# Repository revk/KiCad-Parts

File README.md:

# KiCad-Parts

Now on [CodeBerg](https://codeberg.org/RevK/KiCad-Parts)

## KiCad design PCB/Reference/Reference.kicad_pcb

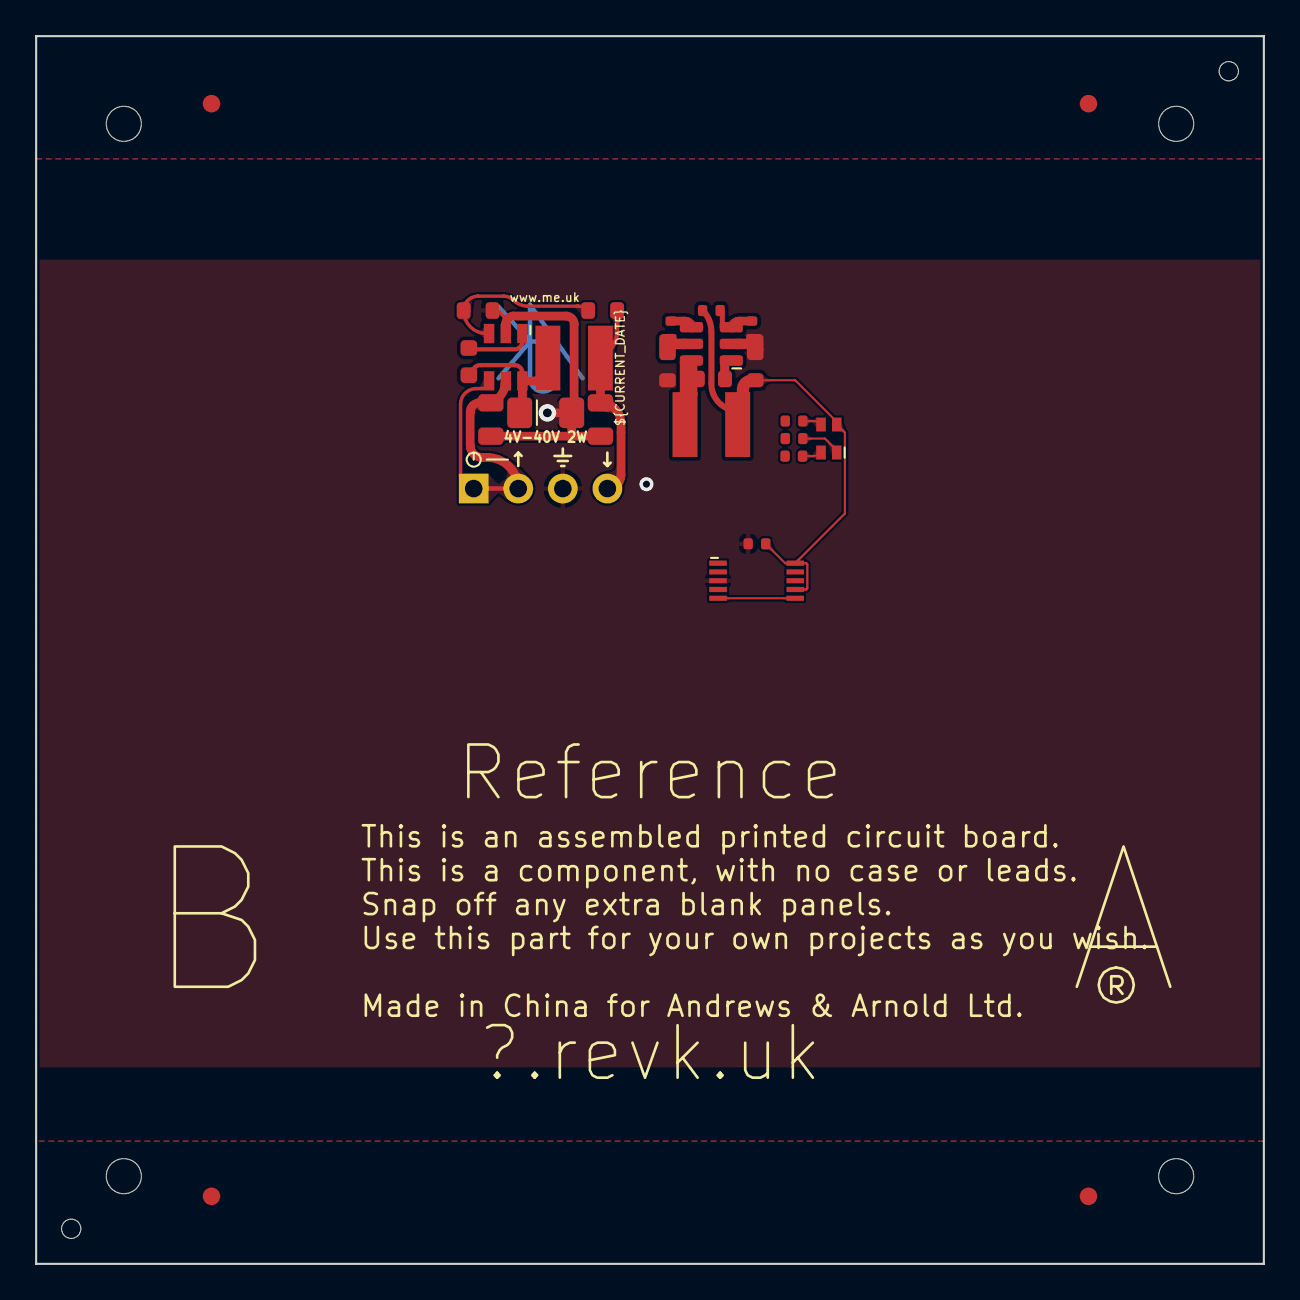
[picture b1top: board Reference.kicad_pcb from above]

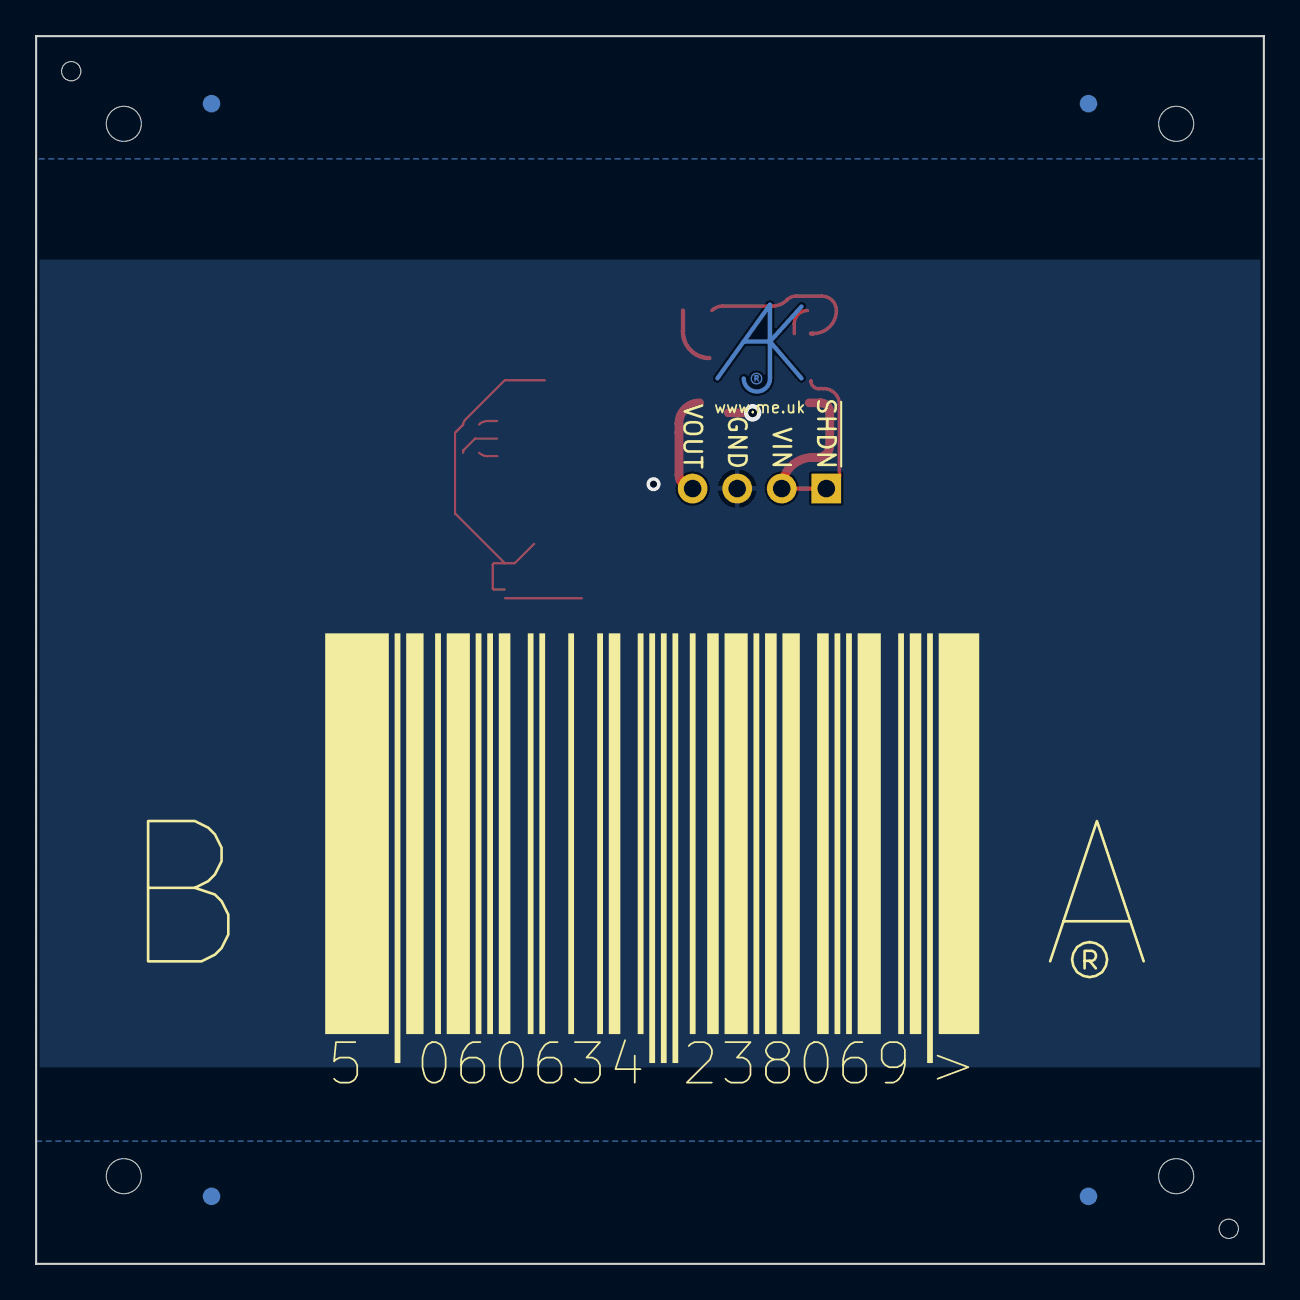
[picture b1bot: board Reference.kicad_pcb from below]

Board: 2 copper layers, 70.0 x 70.0 mm, 28 parts (2 on the bottom side), 9 nets.

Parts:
C1, C6: 100nF; C_0603_
C2: 2.2uF; C_0805_
C3: 10uF; C_0805_
C4: 10uF 50V; C_0603_
C5: 10uF 6.3V; C_0603_
C7: 0.1uF; C_0402
D1: Schottky; D_1206_
D2: RGB; LED-RGB-1.6x1.6
J1: Conn_01x04; JLC-PinHeader_1x04_P2.54mm_Right
L1: 6.8uH; L_4x4_
L2: 10uH; L_4x4_
Logo1: AJK
PCB1: 70x70; PCB7070
R1: 100k 1%; R_0603
R2: 30k 1%; R_0603
R3: 124k; R_0402_
R4: 40k2; R_0402_
R5: 1M; R_0402_
R6: 680R; R_0402
R7: 2K; R_0402
R8: 220R; R_0402
U1: LMR16006XDDCR; SOT-23-Thin-6-Reg
U2: MD8942; SOT-23-6-MD8942
U3: Barcode; EAN-5060634238069
U4: CH340X
V1, V2: VCUT70

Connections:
+3.3V: C7.1, D2.4 (A), U2.8 (VOUT), U4.7 (VCC), U4.10 (V3)
BOOT: U4.5 (~CTS), U4.6 (TNOW/~DTR)
GND: C7.2, J1.3, R2.1, U1.2 (GND), U2.2 (GND), U2.7 (GND), U4.3 (GND)
unnamed: D2.2 (BK), R8.1
unnamed: D2.3 (GK), R7.1
unnamed: D2.1 (RK), R6.1
unnamed: J1.1, J1.2, U1.4 (SHDN), U1.5 (VIN)
unnamed: J1.4, R1.1, U1.7 (VOUT)
unnamed: R1.2, R2.2, U1.3 (FB)

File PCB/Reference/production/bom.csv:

Designator,Footprint,Quantity,Value,LCSC Part #
C1,C_0603_,1,100nF,C30926
C2,C_0805_,1,2.2uF,C19110
C3,C_0805_,1,10uF,C17024
C4,C_0603_,1,10uF 50V,C1591
C5,C_0603_,1,10uF 6.3V,C1691
C6,C_0603_,1,100nF,
C7,C_0402,1,0.1uF,
D1,D_1206_,1,Schottky,C143805
D2,LED-RGB-1.6x1.6,1,RGB,C264508
J1,JLC-PinHeader_1x04_P2.54mm_Right,1,Conn_01x04,C91552
L1,L_4x4_,1,6.8uH,C354575
L2,L_4x4_,1,10uH,
R1,R_0603,1,100k 1%,C14675
R2,R_0603,1,30k 1%,C100001
R3,R_0402_,1,124k,
R4,R_0402_,1,40k2,
R5,R_0402_,1,1M,
R6,R_0402,1,680R,
R7,R_0402,1,2K,
R8,R_0402,1,220R,
U1,SOT-23-Thin-6-Reg,1,LMR16006XDDCR,C87080
U2,SOT-23-6-MD8942,1,MD8942,C2684786
U4,CH340X,1,CH340X,C3035748

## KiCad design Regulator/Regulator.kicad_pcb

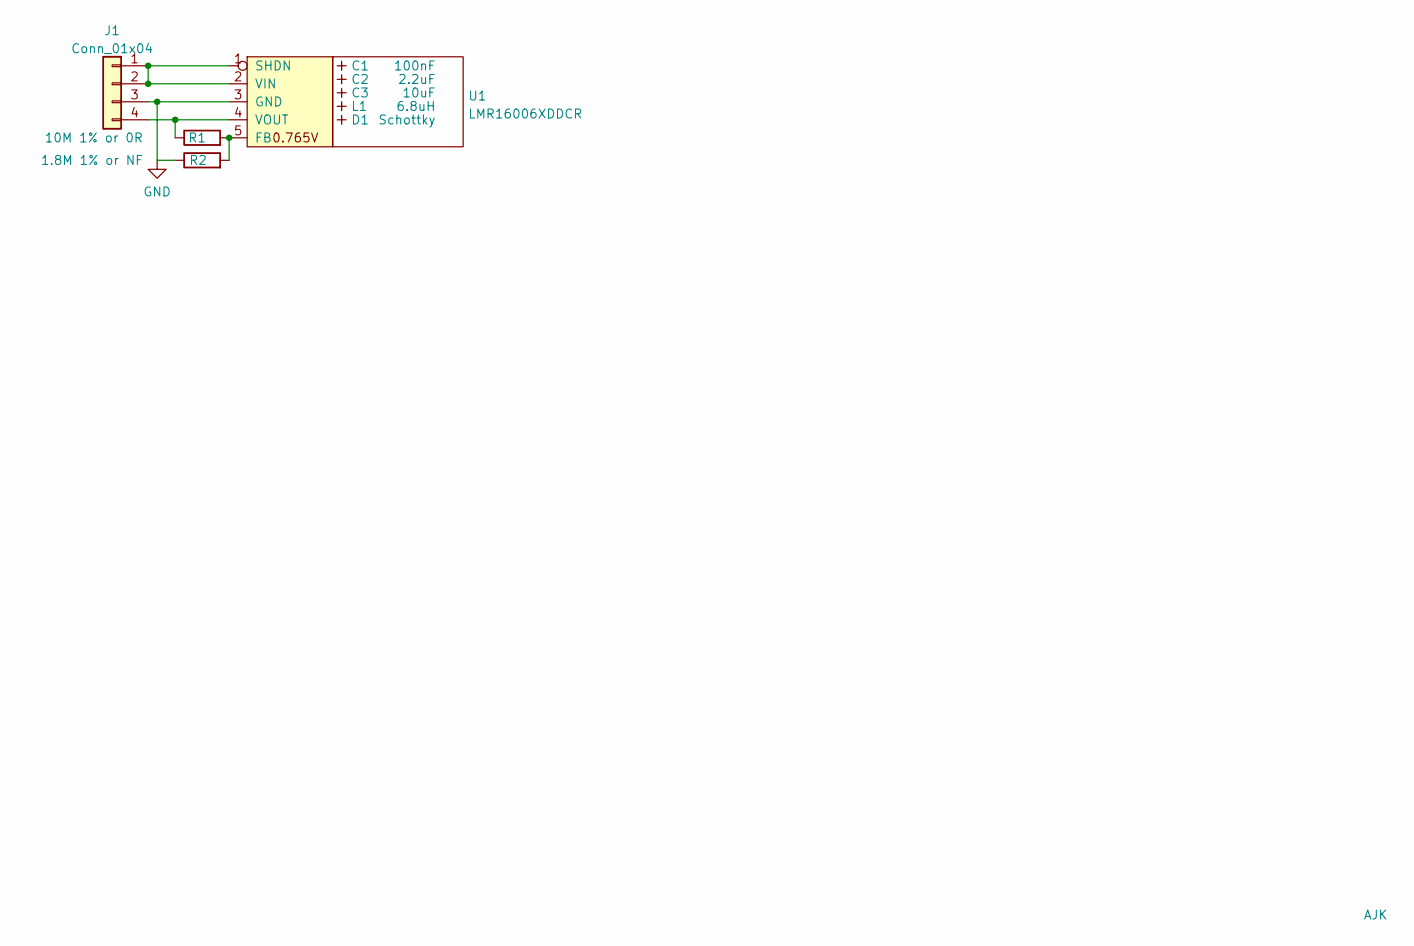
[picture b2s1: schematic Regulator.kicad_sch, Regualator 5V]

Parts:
C1: 100nF; C_0603_
C2: 2.2uF; C_0805_
C3: 10uF; C_0805_
D1: Schottky; D_1206_; Part No CD1206-B2100
J1: Conn_01x04; PinHeader_1x04_P2.54mm_Vertical
L1: 6.8uH; L_4x4_; Part No TYA4020
Logo1: AJK
R1: 10M 1% or 0R; R_0603
R2: 1.8M 1% or NF; R_0603
U1: LMR16006XDDCR; SOT-23-Thin-6-Reg; LCSC Part C87080

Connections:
GND: J1.3, R2.1, U1.3 (GND)
unnamed: J1.1, J1.2, U1.1 (SHDN), U1.2 (VIN)
unnamed: J1.4, R1.1, U1.4 (VOUT)
unnamed: R1.2, R2.2, U1.5 (FB)

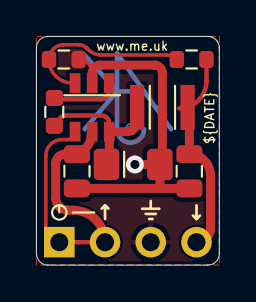
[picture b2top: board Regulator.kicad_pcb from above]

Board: 2 copper layers, 10.2 x 12.7 mm, 10 parts (1 on the bottom side), 4 nets.

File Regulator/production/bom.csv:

Designator,Footprint,Quantity,Value,LCSC Part #
C1,C_0603_,1,100nF,C30926
C2,C_0805_,1,2.2uF,C19110
C3,C_0805_,1,10uF,C17024
D1,D_1206_,1,Schottky,C143805
J1,PinHeader_1x04_P2.54mm_Right,1,Conn_01x04,C91552
L1,L_1210_,1,6.8uH,C560045
R1,R_0603,1,10M 1%,C7250
R2,R_0603,1,1.8M 1%,C137772
U1,SOT-23-Thin-6-Reg2,1,LMR16006XDDCR,C87080

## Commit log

2021-05-24 Started
2021-05-24 Logo
2021-05-27 Solid fill
2021-05-28 Added variable regulator block (external potential divide)
2021-05-31 New idea
2021-05-31 Tweak
2021-06-12 Tweaks to library
2021-06-12 More
2021-06-17 New part
2021-06-17 Non hand version
2021-06-18 Better thermal on USB pads
2021-06-19 Redraw with fewer pads
2021-06-19 Some find tuning
2021-06-20 Tidy
2021-06-29 Neater
2021-07-20 Various tidy
2021-08-06 Tweaks
2021-08-07 Add shelly QR
2021-08-07 New block logic for BOM
2021-08-07 Backups
2021-08-26 Tidy up
2021-11-06 More QRs
2021-11-13 Allow for 3D printed support to align
2021-12-29 KIcad 6
2021-12-29 Kicad 6 fixes
2021-12-29 More Kicad 6 stuff
2021-12-31 Tidy up for kicad 6
2021-12-31 More Kicad 6 tweaks
2022-01-01 BOM/Pos
2022-01-01 Ignore
2022-01-03 Smaller hole, plated
2022-01-18 Tidy up for variable regulators
2022-01-23 SOT457
2022-02-09 Change pads a tad
2022-02-17 SCD41
2022-02-18 Tweak artwork
2022-02-19 Finish off PCB for this
2022-02-19 Reverse
2022-02-20 Library update
2022-02-21 Tidy up SHDN
2022-02-21 Missing from kicad!
2022-02-25 Lots of tidying
2022-03-03 Position/silkscreen
2022-03-06 Clean up
2022-03-11 Revised rules
2022-03-14 Typo
2022-03-18 Joint
2022-05-03 New defaults
2022-05-19 Silkscreen
2022-06-22 Tweaks and new antenna
2022-06-28 Tidy regulator
2022-07-02 Tidy regulator stuff
2022-08-05 Tidy up crystal and add switches
2022-08-05 New detection switches
2022-08-05 Adjust for tamper, and tweak USB
2022-10-06 KiCad uese 0.1"
2023-01-07 Part
2023-01-08 New production files
2023-01-08 Working on assembly files
2023-01-08 Corrected orientation
2023-01-08 Renamed
2023-01-09 Shorter
2023-01-09 Date
2023-01-09 Put back regulator
2023-01-11 Tweaks for production
2023-01-11 Date update
2023-01-11 Added + to SS
2023-02-14 New QR
2023-03-25 PTSM
2023-03-25 New connectors
2023-03-25 More footprints
2023-03-25 More connectors
2023-03-25 pin number
2023-03-25 New connector
2023-03-29 Smaller
2023-04-13 Test board
2023-05-12 Not 6.0
2023-05-14 Cleaner
2023-05-31 Tidy QR
2023-06-02 ESP32-PICO-V3-02, etc
2023-06-18 VEML6040, etc
2023-06-18 Tidy silk
2023-06-18 Pin 1 silk changes
2023-06-19 CH340K
2023-06-19 Tidy again
2023-06-20 CH340X and tweak shelly
2023-06-20 Allow 0.2 clearance on silk
2023-06-20 More SS clearance
2023-06-20 SIlk
2023-06-23 New reg
2023-06-23 Improved
2023-06-23 Pin to 0.1mm for passives
2023-06-23 Add new reg, and tidy
2023-06-25 KiCad
2023-06-25 Hight 15
2023-06-25 Full height
2023-06-25 Hole
2023-06-26 Make
2023-06-27 PCB templatge
2023-06-27 5060634238113
2023-06-28 VCut
2023-06-28 CH340X DTR
2023-06-29 Fix RGB and tidy
2023-07-12 More clearance, etc
2023-07-31 New ESP32
2023-08-01 Correct schematic
2023-08-02 Themal
2023-08-03 Tweak fill
2023-08-05 New bar
2023-08-05 No longer needed
2023-08-07 USB-PROG, etc
2023-08-10 Nedw
2023-09-02 Smaller as may be lots of them
2023-10-14 My own limits
2023-10-15 2 places
2023-10-15 tooling
2023-10-26 More symbols
2023-11-05 Better plug
2023-11-18 New parts
2024-01-02 MicroSD
2024-01-02 Connectors
2024-01-02 Tweak 3D
2024-01-03 Moved
2024-01-19 More circuits
2024-06-04 Moved stuff, etc
2024-06-06 Alignment
2024-06-08 New USB
2024-07-13 Playing with VRML, and other tweaks
2024-07-15 Shadow background
2024-07-15 Holes
2024-07-31 Correct size
2024-08-10 New footprints
2024-08-10 Placement
2024-08-11 Fine tuned position
2024-08-25 Tidy mic
2024-08-30 IR Receiver
2024-11-09 Misc
2024-11-11 MAX98357
2024-11-11 Totadt
2024-12-06 Speaker
2024-12-11 Outside
2024-12-12 Cleaned up
2025-01-22 New KiCAD
2025-01-28 General update
2025-01-31 Cleanup
2025-02-04 Reworked
2025-05-02 Updatye
2025-05-02 Header
2025-07-11 Latest tweaks
2025-08-13 Tidy clearances
2025-10-08 more models
2025-11-27 Latest
2026-01-31 PS-58
